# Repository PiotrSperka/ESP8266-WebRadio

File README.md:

# **ESP8266-WebRadio** #
###WiFi shoutcast player based on ESP8266 chip
##Basic informations
Version: 0.18<br />
Status: under design and development
##Used hardware
WiFi and main MCU: ESP8266 (ESP-12 with 32Mbits flash)<br />
Additional MCU (as a UART<=>UI bridge): AVR<br />
Audio decoder: VS1053<br />
##TODO list
-**[HIGH]**LCD and encoder <=> UART converter based on AVR (ATmega88?)<br />
-**[NORMAL]**FM module (RDA5807M) implementation<br />
-**[NORMAL]**Reconnect to webradio when internet connection reappears<br />
-**[LOW]**Code cleanup and optimization
##Changelog
###v0.18
-**[ESP8266]**External SRAM is now implemented and it is set by deafult as place for audio buffer. However, operation without external SRAM is still possible (please refer to buffer.h)
###v0.17
-**[MERGE]**Merged with karawin's fork (version 1.0.4)<br />
He made lots of changes, especially he improved stability and webpage user experience. For details please visit his Github webpage:<br />
https://github.com/karawin/Ka-Radio
###v0.16
-**[Hardware]**Slightly updated GERBER files
###v0.15
-**[ESP8266]**Metadata processing
###v0.14
-**[MERGE]**Merged with karawin's fork, he made following changes:<br />
-New development based on the new https://github.com/espressif/ESP8266_RTOS_SDK<br />
-Software improved, new web control<br />
-Compatible with mobile<br />
-Stable<br />
-Tools to save and restore the stations database
###v0.13
-**[ESP8266]**Some kind of beta version of web interface is ready.<br />
-**[ESP8266]**Works saving and loading stations and settings to/from flash<br />
-**[ESP8266]**Added "How to run" document
###v0.12
-**[ESP8266]**Development of functions for saving and reading settings from flash "eeprom"<br />
-**[ESP8266]**Functions for driving GPIO16<br />
-**[ESP8266]**Development of webinterface<br />
-**[ESP8266]**Webclient is using socket
###v0.11
-**[Hardware]**Finished first revision of schematic (main board) and PCB<br />
-**[Hardware]**Added GERBER files for main board (NOT TESTED YET)<br />
-**[Hardware]**AVR is going to be only an interface between UART in ESP8266 and UI (which is LCD, encoder and buttons)
###v0.10
-**[ESP8266]**Support for user data (stations, config, etc.) storage in last 64kb of flash<br />
-**[Hardware]**Schematic of main board
###v0.9
-**[ESP8266]**Sound settings through web interface<br />
-**[ESP8266]**Web interface improvements
###v0.8
-**[ESP8266]**Webserver uses sockets - improved stability<br />
-**[ESP8266]**Improvments of webinterface (now supports Instant Play)<br />
-**[ESP8266]**Improvments of webserver (simple POST parser)<br />
-**[ESP8266]**DNS lookup
###v0.7
-**[ESP8266]**Simple and rough sketch of VS1053 driver (working)<br />
-**[ESP8266]**Rough sketch of webclient is working<br />
-I can say that alpha version of player works for now, because I can listen to some SHOUTcast streams.
###v0.6
-**[ESP8266]**Started making new firmware based on esp_iot_rtos_sdk with bare LwIP and freeRTOS<br />
-**[Hardware]**New conception of hardware, where main MCU is ESP8266 and some small AVR is only to provide user interface (LCD, etc.) and configure ESP via UART<br />
-First tests of new firmware are very promising, because HTTP server based on Netconn is very responsive (much better than previous version of firmware)
###v0.5
-**[ESP8266]**Improved: HTTP server configuration<br />
-**[ESP8266]**Added: HTTP client UART output<br />
-**[STM32]**Added: Unclean sketch of firmware for basic testing purposes
###v0.4
-**[ESP8266]**Added: Simple CGI parser<br />
-**[ESP8266]**Added: ICY header parser
###v0.3
-**[ESP8266]**Added: Simple admin panel mockup<br />
-**[ESP8266]**Added: Connecting to client
###v0.2
-**[ESP8266]**Added: Running simple http server on port 80<br />
-**[ESP8266]**Added: Simple UART command parser for wifi configuration
###v0.1
-**[ESP8266]**Initial release - ESP8266 firmware based on cleaned nodemcu source (deleted lua, flash-fs, etc.)

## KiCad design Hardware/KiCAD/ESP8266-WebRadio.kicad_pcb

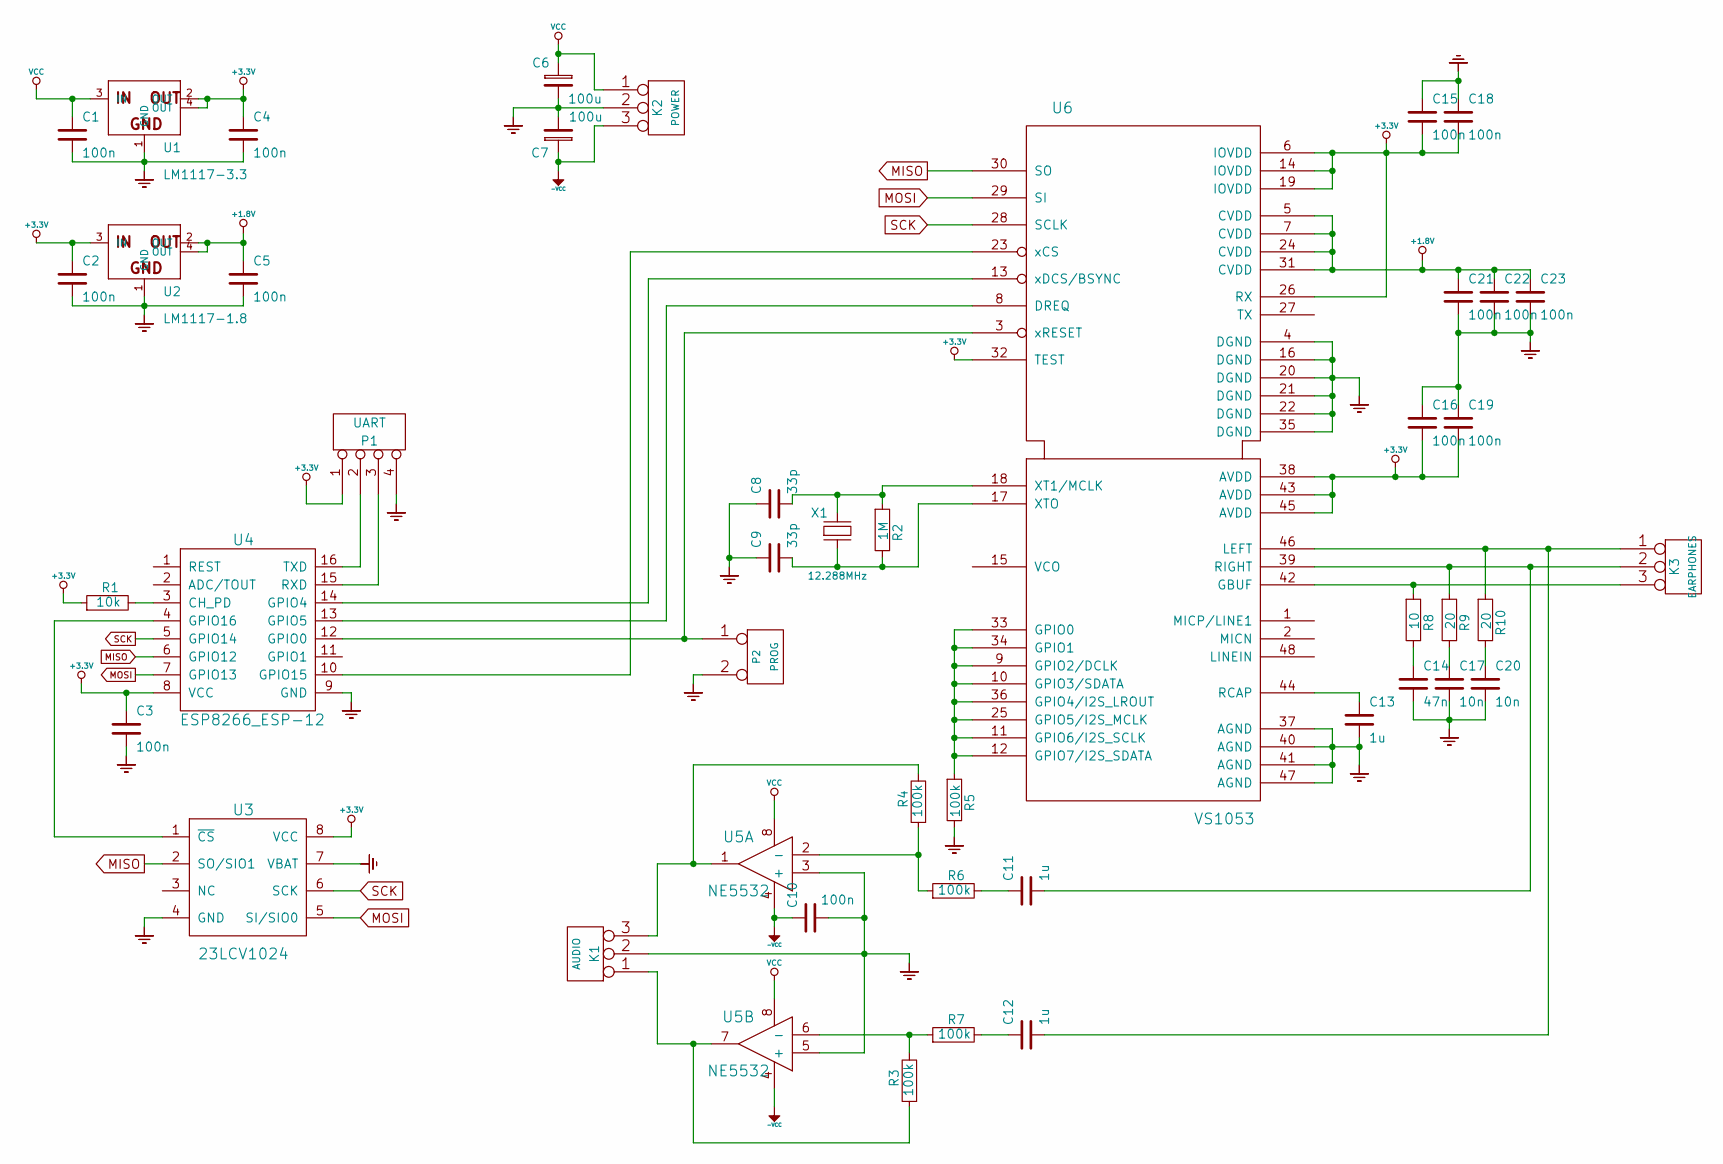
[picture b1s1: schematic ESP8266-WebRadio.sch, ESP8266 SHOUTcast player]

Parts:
C1, C2, C3, C4, C5, C10, C15, C16, C18, C19, C21, C22, C23: 100n
C6, C7: 100u
C8, C9: 33p
C11, C12, C13: 1u
C14: 47n
C17, C20: 10n
K1: AUDIO
K2: POWER
K3: EARPHONES
P1: UART
P2: PROG
R1: 10k
R2: 1M
R3, R4, R5, R6, R7: 100k
R8: 10
R9, R10: 20
U1: LM1117-3.3
U2: LM1117-1.8
U3: 23LCV1024
U4: ESP8266_ESP-12
U5: NE5532
U6: VS1053
X1: 12.288MHz

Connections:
+1.8V: C5.1, C21.1, C22.1, C23.1, U2.2 (OUT), U2.4 (OUT), U6.5 (CVDD), U6.7 (CVDD), U6.24 (CVDD), U6.31 (CVDD)
+3.3V: C2.1, C3.1, C4.1, C15.2, C16.2, C18.2, C19.2, P1.1, R1.1, U1.2 (OUT), U1.4 (OUT), U2.3 (IN), U3.8 (VCC), U4.8 (VCC), U6.6 (IOVDD), U6.14 (IOVDD), U6.19 (IOVDD), U6.26 (RX), U6.32 (TEST), U6.38 (AVDD), U6.43 (AVDD), U6.45 (AVDD)
-6V: C7.1, C10.1, K2.3, U5.4
GND: C1.2, C2.2, C3.2, C4.2, C5.2, C6.2, C7.2, C8.1, C9.1, C10.2, C13.2, C14.2, C15.1, C16.1, C17.2, C18.1, C19.1, C20.2, C21.2, C22.2, C23.2, K1.2 (PM), K2.2 (PM), P1.4, P2.2 (PM), R5.2, U1.1 (GND), U2.1 (GND), U3.4 (GND), U3.7 (VBAT), U4.9 (GND), U5.3 (+), U5.5 (+), U6.4 (DGND), U6.16 (DGND), U6.20 (DGND), U6.21 (DGND), U6.22 (DGND), U6.35 (DGND), U6.37 (AGND), U6.40 (AGND), U6.41 (AGND), U6.47 (AGND); also elsewhere on the board
MISO: U3.2 (SO/SIO1), U4.6 (GPIO12), U6.30 (SO)
MOSI: U3.5 (SI/SIO0), U4.7 (GPIO13), U6.29 (SI)
unnamed: C13.1, U6.44 (RCAP)
unnamed: R5.1, U6.9 (GPIO2/DCLK), U6.10 (GPIO3/SDATA), U6.11 (GPIO6/I2S_SCLK), U6.12 (GPIO7/I2S_SDATA), U6.25 (GPIO5/I2S_MCLK), U6.33 (GPIO0), U6.34 (GPIO1), U6.36 (GPIO4/I2S_LROUT)
unnamed: C11.1, R6.2
unnamed: C12.1, R7.2
unnamed: C11.2, K3.2 (PM), R9.1, U6.39 (RIGHT)
unnamed: C12.2, K3.1, R10.1, U6.46 (LEFT)
unnamed: U3.1 (~CS), U4.4 (GPIO16)
unnamed: P2.1, U4.12 (GPIO0), U6.3 (xRESET)
unnamed: K1.3, R4.2, U5.1
unnamed: R4.1, R6.1, U5.2 (-)
unnamed: K1.1, R3.1, U5.7
unnamed: R3.2, R7.1, U5.6 (-)
unnamed: C20.1, R10.2
unnamed: C17.1, R9.2
unnamed: C14.1, R8.2
unnamed: K3.3, R8.1, U6.42 (GBUF)
unnamed: C8.2, R2.1, U6.18 (XT1/MCLK), X1.2
unnamed: C9.2, R2.2, U6.17 (XTO), X1.1
unnamed: R1.2, U4.3 (CH_PD)
unnamed: U4.10 (GPIO15), U6.23 (xCS)
unnamed: U4.14 (GPIO4), U6.13 (xDCS/BSYNC)
unnamed: U4.13 (GPIO5), U6.8 (DREQ)
unnamed: P1.3, U4.15 (RXD)
unnamed: P1.2, U4.16 (TXD)
SCK: U3.6 (SCK), U4.5 (GPIO14), U6.28 (SCLK)
VCC: C1.1, C6.1, K2.1, U1.3 (IN), U5.8

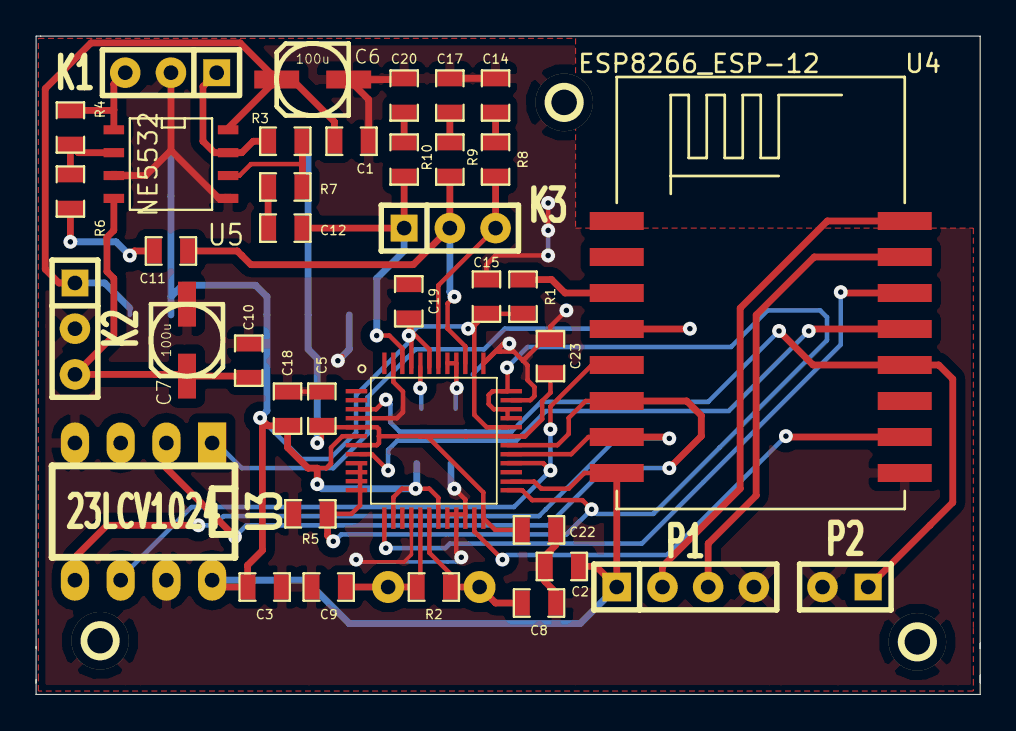
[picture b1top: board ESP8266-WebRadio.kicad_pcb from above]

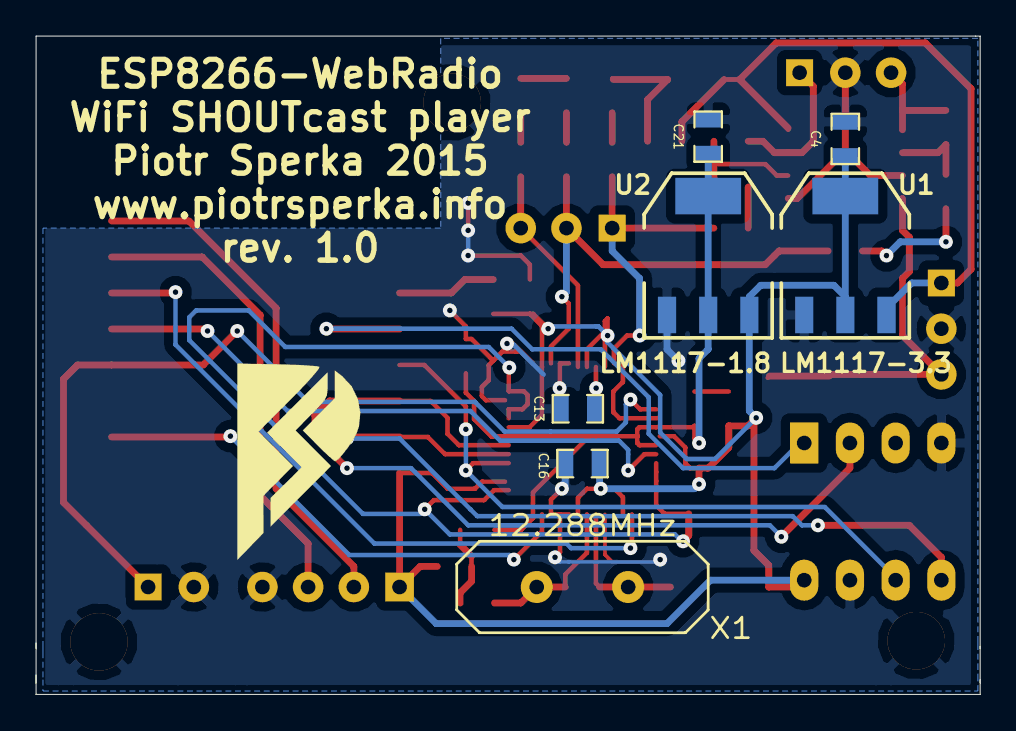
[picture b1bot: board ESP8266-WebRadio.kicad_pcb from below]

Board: 2 copper layers, 52.5 x 36.6 mm, 48 parts (7 on the bottom side), 32 nets.

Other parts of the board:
1PIN, 1PIN#2: P***; 1pin
VAL: REF; Logo

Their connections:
GND: 1PIN.1, 1PIN#2.1; also elsewhere on the board

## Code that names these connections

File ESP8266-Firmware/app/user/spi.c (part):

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		PIN_FUNC_SELECT(PERIPHS_IO_MUX_SD_DATA1_U, 1);	
	}else if(spi_no==HSPI){
		WRITE_PERI_REG(PERIPHS_IO_MUX, 0x105|(clock_div_flag<<9)); //Set bit 9 if 80MHz sysclock required
		PIN_FUNC_SELECT(PERIPHS_IO_MUX_MTDI_U, 2); //GPIO12 is HSPI MISO pin (Master Data In)
		PIN_FUNC_SELECT(PERIPHS_IO_MUX_MTCK_U, 2); //GPIO13 is HSPI MOSI pin (Master Data Out)
		PIN_FUNC_SELECT(PERIPHS_IO_MUX_MTMS_U, 2); //GPIO14 is HSPI CLK pin (Clock)
		//PIN_FUNC_SELECT(PERIPHS_IO_MUX_MTDO_U, 2); //GPIO15 is HSPI CS pin (Chip Select / Slave Select)
	}

}
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
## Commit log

2015-03-05 Initial version of ESP8266 firmware based on nodemcu
2015-03-05 Added simple readme and directory structure
2015-03-06 Added support for incoming uart messages and protorype of command parser
2015-03-10 Simple UART command parser (WiFi connection) Simple HTTP server is hosting sample webpage
2015-03-14 Admin panel mockup Server autostart Connection to client
2015-03-15 Added: Simple CGI parser for admin panel Added: ICY header parser
2015-03-23 Added HTTP client UART output Added unclean sketch of STM32 firmware for basic testing purposes Improved HTTP server configuration
2015-08-03 Fresh start with new SDK
2015-08-07 Simple sketch of VS1053 driver Simple and not finished version of webclient
2015-08-07 DNS Resolver Webclient uses functions for setting URL, path and port A little bit of webclient and VS1053 code cleanup
2015-08-07 Repo cleanup
2015-08-08 Improvements of webserver and webinterface DNS resolver
2015-08-08 Webserver uses sockets - improved stability
2015-08-09 Web interface: sound settings and other minior improvements
2015-08-15 Flash data storage
2015-08-15 Added schematic of main board
2015-08-17 Added schematic and PCB of main board
2015-08-23 Development of flash eeprom functions, GPIO16, webinterface changes, webclient is using sockets.
2015-08-28 Beta version of web interface, saving and loading stations and settings.
2015-08-28 Web interface improvements
2015-09-01 Added pullups in schematic and PCB
2016-04-16 Merged with karawin's fork Added metadata parsing
2016-04-17 Added missing KiCad libraries Added missing .a files
2016-04-17 Deleted temp files
2016-06-17 Merged with karawin's fork
2016-06-17 External SRAM is now implemented

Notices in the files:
ESP8266-Firmware/app/user/spi.c:
The MIT License (MIT)
Copyright (c) 2015 David Ogilvy (MetalPhreak)
